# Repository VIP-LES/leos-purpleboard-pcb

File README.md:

# LEOS Purpleboard

The Purpleboard holds four environmental and light sensors, powered at 3.3 V. The board has no microcontroller instead it connects to a host board through a JST XH cable, and a second JST XH connector passes the I2C bus and power through to another board.

**Current revision:** 2.1

## Sensors

| Ref | Sensor | Measures | Header | Default I²C address |
|-----|--------|----------|--------|---------------------|
| J2 | BME688 | Temperature, humidity, pressure, gas | 7-pin | 0x77 |
| J3 | LTR390 | UV and ambient light | 6-pin | 0x53 |
| J4 | PMSA003I | Air Quality (PM1.0, PM2.5, PM10) | 7-pin | 0x12 |
| J5 | TSL2591 | High-dynamic-range light | 6-pin | 0x29 |

Each sensor is a breakout board that plugs into a pin header. All four share the same SCL and SDA lines, and their default addresses do not conflict.

## Connectors

| Pin | Signal |
|-----|--------|
| 1 | GND |
| 2 | +3.3 V |
| 3 | SDA |
| 4 | SCL |

## Sensor header wiring

- **VIN** on every header is connected to +3.3 V, and **GND** to ground.
- **SCL/SDA** are connected to the shared I²C bus. On the BME688 these are the SCK and SDI pins.
- Not connected: the 3V output pins on all breakouts, BME688 SDO and CS, LTR390 INT, TSL2591 INT, and PMSA003I RST and SET.

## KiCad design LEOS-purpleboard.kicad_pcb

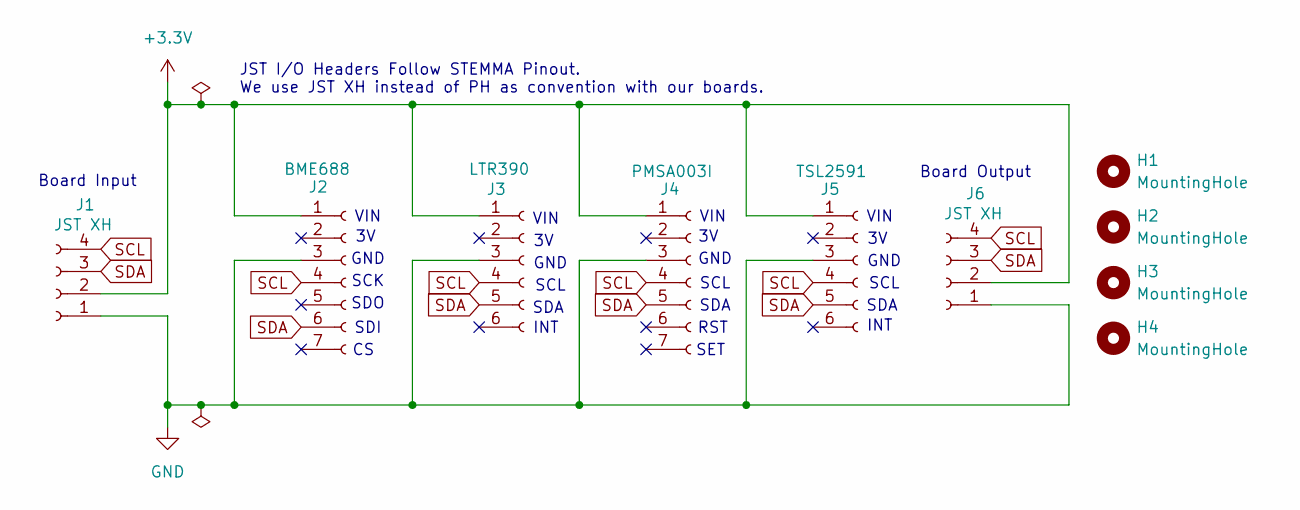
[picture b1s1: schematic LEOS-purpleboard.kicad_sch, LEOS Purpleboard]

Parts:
H1, H2, H3, H4: MountingHole; MountingHole_3.2mm_M3
J1, J6: JST XH; JST_XH_S4B-XH-A_1x04_P2.50mm_Horizontal
J2: BME688; PinHeader_1x07_P2.54mm_Vertical
J3: LTR390; PinHeader_1x06_P2.54mm_Vertical
J4: PMSA003I; PinHeader_1x07_P2.54mm_Vertical
J5: TSL2591; PinHeader_1x06_P2.54mm_Vertical

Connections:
+3.3V: J1.2, J2.1, J3.1, J4.1, J5.1, J6.2
GND: J1.1, J2.3, J3.3, J4.3, J5.3, J6.1
SCL: J1.4, J2.4, J3.4, J4.4, J5.4, J6.4
SDA: J1.3, J2.6, J3.5, J4.5, J5.5, J6.3

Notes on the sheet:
JST I/O Headers Follow STEMMA Pinout. We use JST XH instead of PH as convention with our boards.
SCK
GND
VIN
INT
SDI
SET
SDA
SDO
SCL
Board Output
Board Input
RST

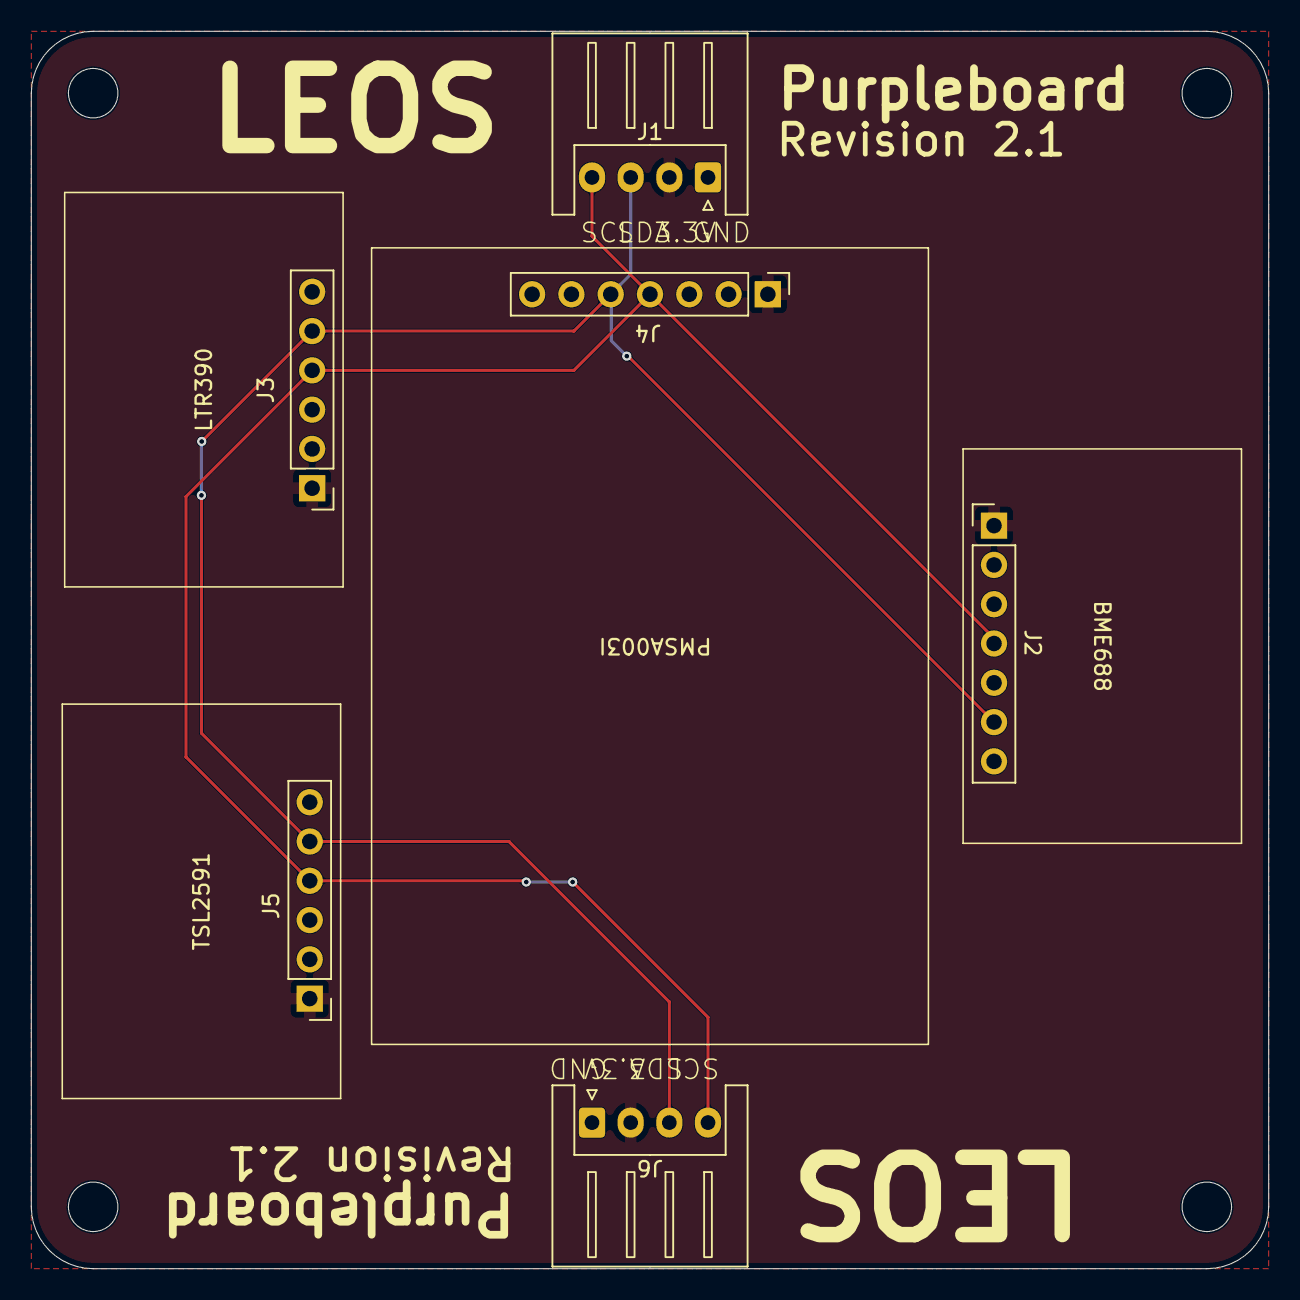
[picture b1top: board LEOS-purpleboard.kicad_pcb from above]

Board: 2 copper layers, 80.0 x 80.0 mm, 10 parts (0 on the bottom side), 4 nets.

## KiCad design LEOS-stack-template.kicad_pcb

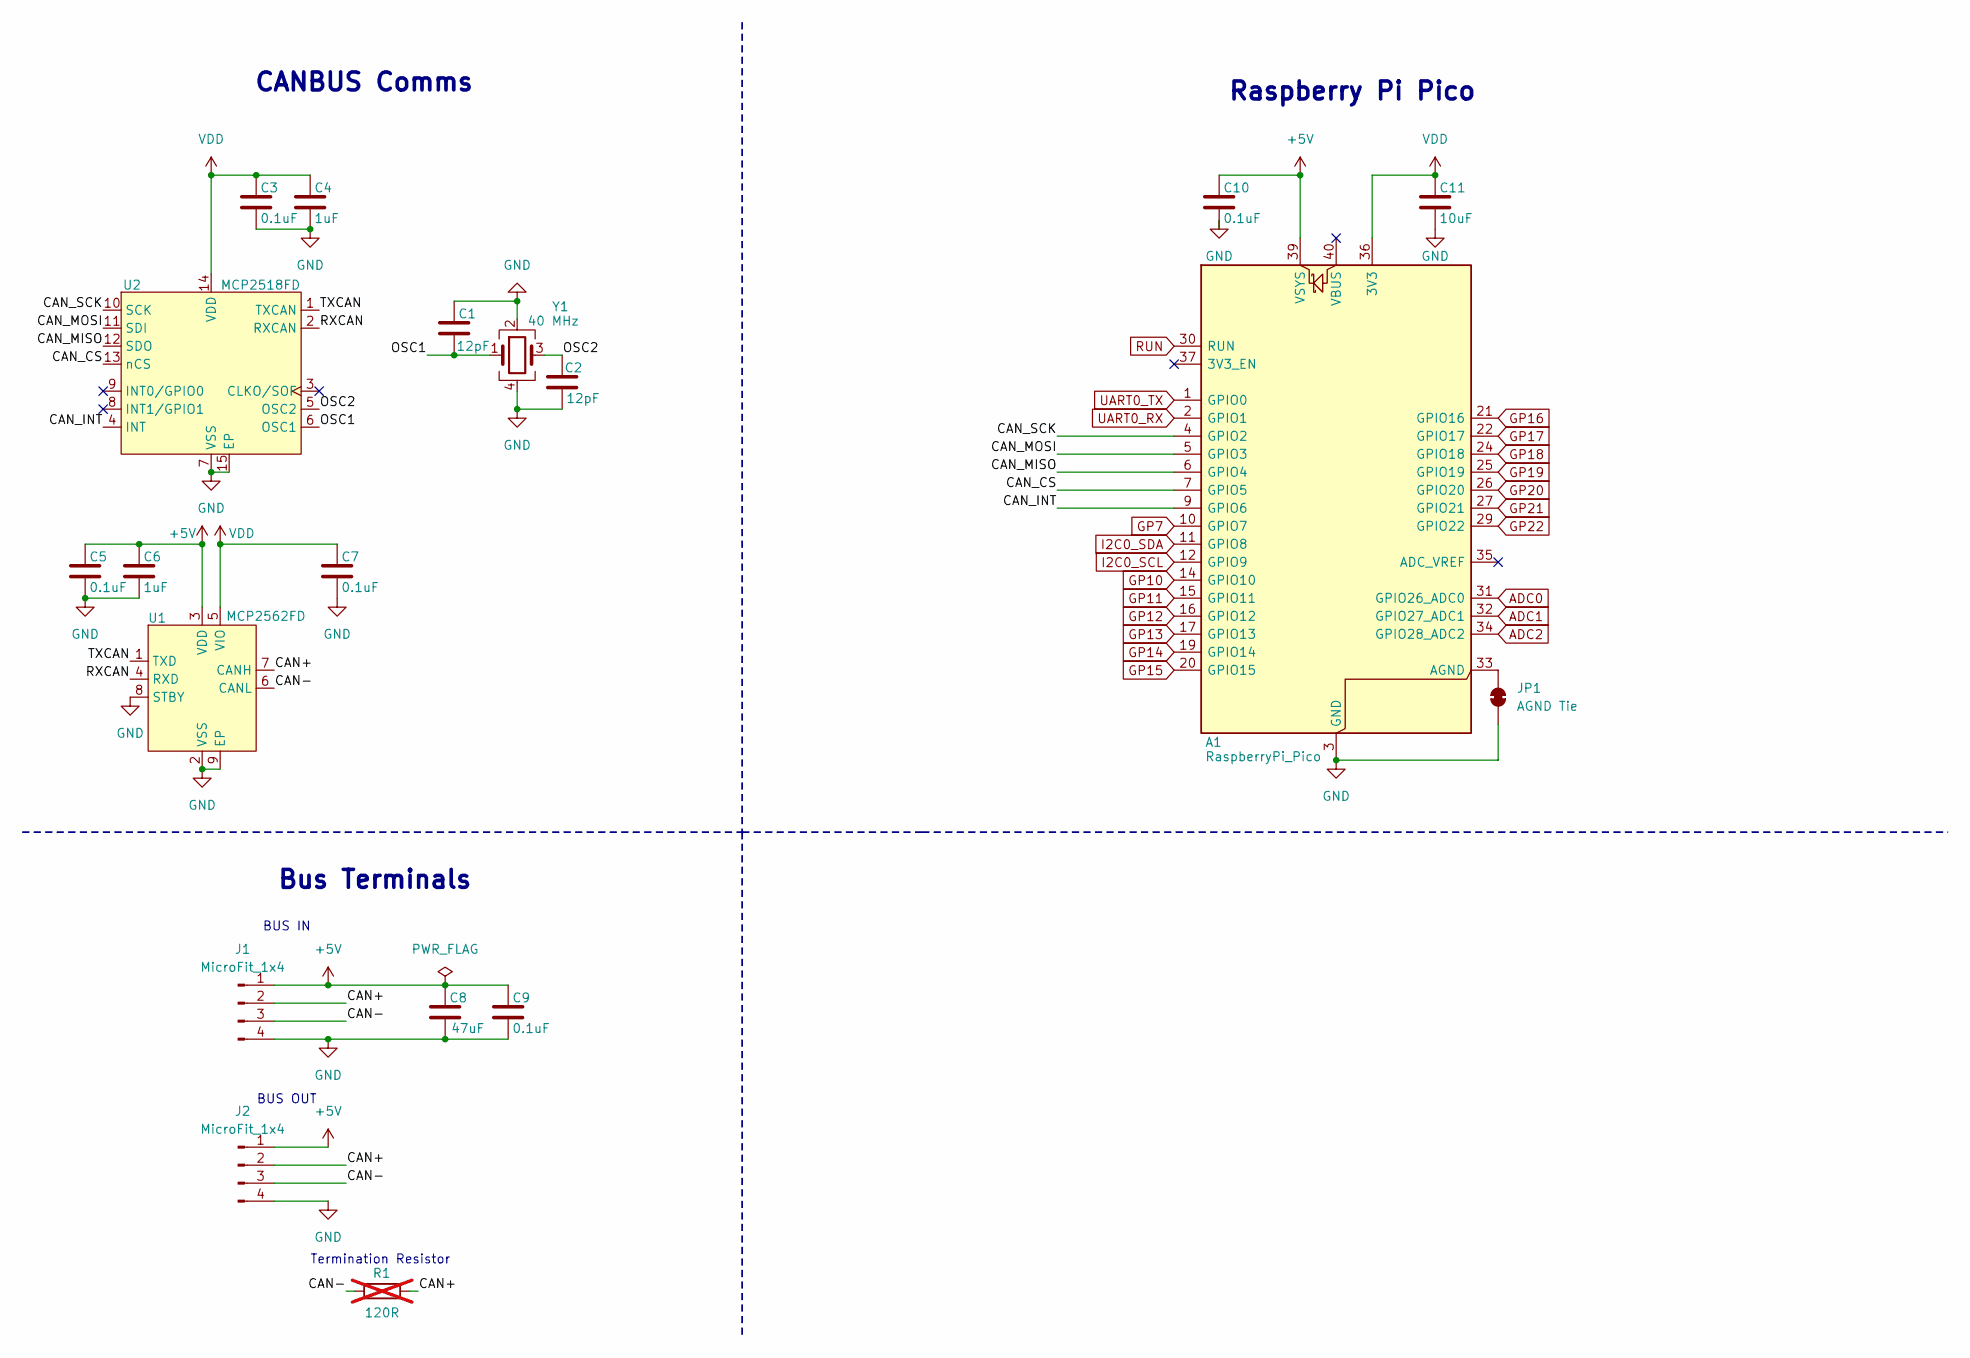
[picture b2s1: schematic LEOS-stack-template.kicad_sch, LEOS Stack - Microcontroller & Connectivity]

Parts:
A1: RaspberryPi_Pico; RaspberryPi_Pico_Common_THT
C1, C2: 12pF; C_0603_1608Metric
C3, C5, C7, C9, C10: 0.1uF; C_0603_1608Metric
C4, C6: 1uF; C_0603_1608Metric
C8: 47uF; C_0603_1608Metric
C11: 10uF; C_0603_1608Metric
J1, J2: MicroFit_1x4; Molex_Micro-Fit_3.0_43650-0410_1x04-1MP_P3.00mm_Horizontal_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
JP1: AGND Tie; SolderJumper-2_P1.3mm_Bridged_RoundedPad1.0x1.5mm
R1: 120R; R_Axial_DIN0207_L6.3mm_D2.5mm_P7.62mm_Horizontal; not fitted
U1: MCP2562FD; SOIC-8_3.9x4.9mm_P1.27mm
U2: MCP2518FD; SOIC-14_3.9x8.7mm_P1.27mm
Y1: 40 MHz; Crystal_SMD_3225-4Pin_3.2x2.5mm_HandSoldering; MPN C13738

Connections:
+5V: A1.39 (VSYS), C5.1, C6.1, C8.1, C9.1, C10.1, J1.1, J2.1, U1.3 (VDD)
/CAN+: J1.2, J2.2, R1.2, U1.7 (CANH)
/CAN-: J1.3, J2.3, R1.1, U1.6 (CANL)
/CAN_CS: A1.7 (GPIO5), U2.13 (nCS)
/CAN_INT: A1.9 (GPIO6), U2.4 (INT)
/CAN_MISO: A1.6 (GPIO4), U2.12 (SDO)
/CAN_MOSI: A1.5 (GPIO3), U2.11 (SDI)
/CAN_SCK: A1.4 (GPIO2), U2.10 (SCK)
/OSC1: C1.1, U2.6 (OSC1), Y1.1
/OSC2: C2.2, U2.5 (OSC2), Y1.3
/RXCAN: U1.4 (RXD), U2.2 (RXCAN)
/TXCAN: U1.1 (TXD), U2.1 (TXCAN)
ADC0: A1.31 (GPIO26_ADC0)
ADC1: A1.32 (GPIO27_ADC1)
ADC2: A1.34 (GPIO28_ADC2)
GND: A1.3 (GND), A1.8 (GND), A1.13 (GND), A1.18 (GND), A1.23 (GND), A1.28 (GND), A1.38 (GND), C1.2, C2.1, C3.2, C4.2, C5.2, C6.2, C7.2, C8.2, C9.2, C10.2, C11.2, J1.4, J2.4, JP1.1 (A), U1.2 (VSS), U1.8 (STBY), U1.9 (EP), U2.7 (VSS), U2.15 (EP), Y1.2, Y1.4
GP7: A1.10 (GPIO7)
GP10: A1.14 (GPIO10)
GP11: A1.15 (GPIO11)
GP12: A1.16 (GPIO12)
GP13: A1.17 (GPIO13)
GP14: A1.19 (GPIO14)
GP15: A1.20 (GPIO15)
GP16: A1.21 (GPIO16)
GP17: A1.22 (GPIO17)
GP18: A1.24 (GPIO18)
GP19: A1.25 (GPIO19)
GP20: A1.26 (GPIO20)
GP21: A1.27 (GPIO21)
GP22: A1.29 (GPIO22)
I2C0_SCL: A1.12 (GPIO9)
I2C0_SDA: A1.11 (GPIO8)
unnamed: A1.33 (AGND), JP1.2 (B)
RUN: A1.30 (RUN)
UART0_RX: A1.2 (GPIO1)
UART0_TX: A1.1 (GPIO0)
VDD: A1.36 (3V3), C3.1, C4.1, C7.1, C11.1, U1.5 (VIO), U2.14 (VDD)

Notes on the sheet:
CANBUS Comms
Raspberry Pi Pico
BUS IN
Termination Resistor
BUS OUT
Bus Terminals

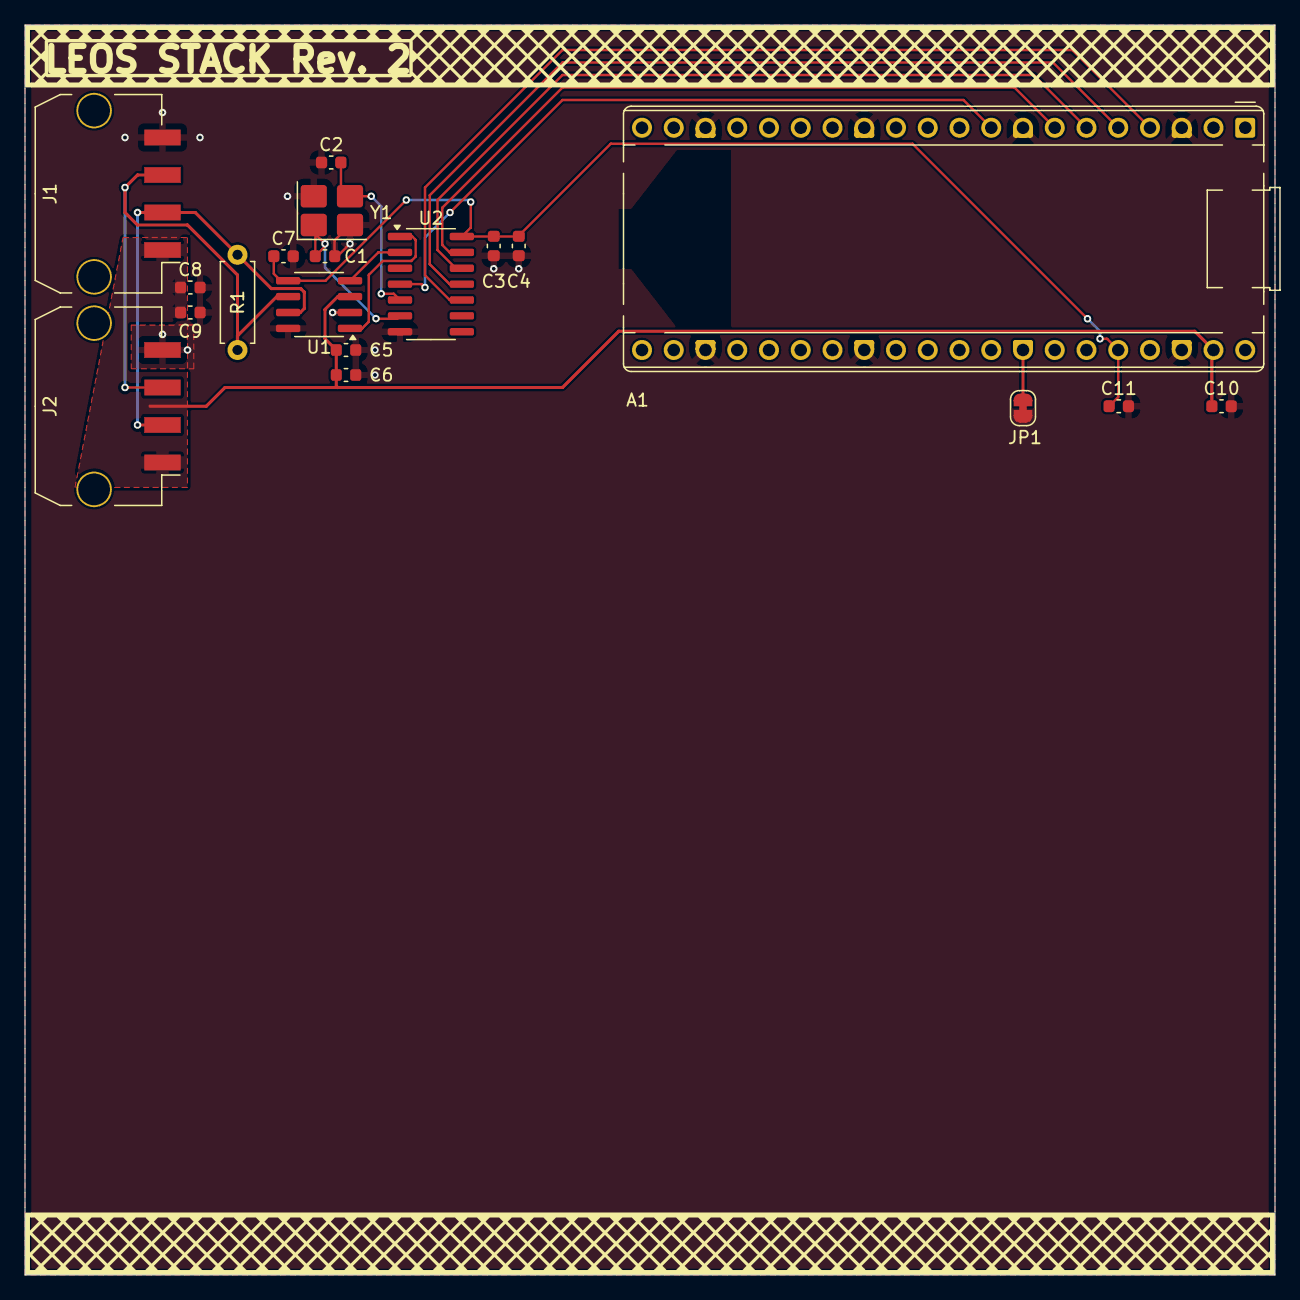
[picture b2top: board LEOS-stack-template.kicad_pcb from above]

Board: 2 copper layers, 100.0 x 100.0 mm, 19 parts (0 on the bottom side), 15 nets.

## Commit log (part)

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2026-02-13 Remove stack template
2026-02-13 Fix flipped pinouts, update 3D model, and redesign schematic
2026-02-17 Add production date to board.
